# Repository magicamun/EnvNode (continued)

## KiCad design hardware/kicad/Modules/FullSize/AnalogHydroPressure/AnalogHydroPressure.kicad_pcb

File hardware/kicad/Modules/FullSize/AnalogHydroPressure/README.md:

# EnvNode AnalogHydroPressure

`AnalogHydroPressure` is a FullSize daughterboard for a two-wire 4–20 mA hydrostatic pressure probe. The current hardware is Revision 0.5, succeeding the legacy `AnalogInput` module.

## Project Files

- `AnalogHydroPressure.kicad_pro`
- `AnalogHydroPressure.kicad_sch`
- `AnalogHydroPressure.kicad_pcb`
- `Analog.kicad_sch` — analog input and ADS1115
- `24VBoost.kicad_sch` — local probe-supply generation
- `Documentation/AnalogHydroPressure_Bestueckungs_und_Bringup_Rev0.5.pdf` — assembly, configuration, and bring-up guide

## Functional Structure

The module has two hierarchical circuit sections:

- The analog section converts the probe loop current across a 150 ohm, 0.1% burden resistor, filters and clamps the signal, and digitizes it with an `ADS1115IDGS` on the I2C bus selected by JP5 (SDA) and JP6 (SCL).
- The boost section uses an `LT8330S6` to generate the local 24 V probe rail from the module interface's `+5V` supply.

The ADS1115 address is selected with one of four solder jumpers for addresses `0x48` through `0x4B`. Exactly one address jumper must be closed before operation.

JP5 (SDA) and JP6 (SCL) select the ADS1115 bus. Bridge pins 1-2 on both for I2C0, or pins 2-3 on both for I2C1. Both jumpers must select the same bus. Without both bridges the ADS1115 is disconnected from the bus. Never bridge all three pins or mix the bus selections. These jumpers do not select the 5 V supply. The identity EEPROM remains on I2C0.

## Local Libraries

The LT8330 symbol is stored in:

`hardware/kicad/Libraries/EnvNode-Symbols.kicad_sym`

The C&K switch footprint is stored in:

`hardware/kicad/Libraries/EnvNode-Footprints.pretty/SW_Slide_CK_OS202011MS2QS1.kicad_mod`

The project-level `sym-lib-table` maps the symbol library. The footprint library name must resolve as `EnvNode-Footprints` in KiCad.

The analog measurement path remains electrically functional without the identity EEPROM. Without a valid module descriptor, firmware cannot identify the module, validate compatibility or derive module-specific settings. ADC acquisition and boost control then require explicit manual configuration and suitable driver support.

## Bring-up Priorities

1. Populate and inspect the 5 V input and LT8330 boost section.
2. Power it from a current-limited 5 V supply before connecting a probe.
3. Verify startup, switching waveform, output voltage, ripple, and component temperature under the intended load.
4. Verify that exactly one ADS1115 address jumper is closed and that the ADC is detected on the I2C bus selected by JP5 (SDA) and JP6 (SCL).
5. Apply known loop currents and verify approximately 0.6 V at 4 mA and 3.0 V at 20 mA across the nominal 150 ohm burden.
6. Verify the bottom-side U3 (24LC32A-I/SN, ENP-00102) and C1 (100 nF, ENP-00006), the 3.3 V supply and I2C0 address 0x52 (Slot A) or 0x53 (Slot B). Validate the module descriptor; an I2C response alone does not confirm provisioning. Use a matching descriptor, never the DuoRelay template.
7. Calibrate the complete measurement path with the intended pressure probe.

## Validation and Release Status

Revision 0.4 uses the B260S1F-7 boost diode, selectable ADS1115 address jumpers, and an optional DNP measurement header for GND, `+24V`, `LOOP_RETURN`, and `AIN0`. The bottom-side identification EEPROM U3 and its 100 nF decoupling capacitor C1 are part of the standard assembly. J2 remains optional / DNP. The PCB remains Revision 0.5.

At the historical design checkpoint on 2026-09-28, schematic ERC and PCB DRC completed without errors or violations, schematic/PCB parity was clean, and the layout received a visual plausibility review. These checks do not replace physical power-supply bring-up, thermal and EMC verification, probe calibration, or production testing.

The Revision 0.5 assembly/bring-up guide documents AUX_GPIO2 / connector pin 10 for boost enable, including continuity checks, startup sequencing, updated PCB views, and source hashes. Revision 0.4 remains available as a historical guide; its article list predates the enable reassignment. Physical boost-converter validation, thermal and EMC verification, probe calibration, and production testing remain required before production release.

## Connector review — 2026-09-28

The module uses J1 pin 5 for I2C0 SDA and pin 6 for I2C0 SCL. Mini Revision 0.7 and WeatherStation Revision 0.2 both match this assignment in schematic and PCB; the earlier mainboard I2C0 mismatch is resolved for these revisions. I2C1 uses pin 7 SDA and pin 8 SCL and can be selected for the ADS1115 through JP5/JP6.

Revision 0.5 moves LT8330 EN/UVLO and its R7 pull-down to J1 pin 10 / AUX_GPIO2 in both schematic and PCB. J1 pin 9 / AUX_GPIO1 is now unused and available for a future conditioned SCT013 analog signal; no SCT013 circuit is implemented yet. Firmware must use AUX_GPIO2 for boost enable: GPIO13 on Mini Slot A and WeatherStation Slot A, GPIO14 on Mini Slot B. Firmware was not modified as part of this hardware revision.

The Revision 0.5 review on 2026-09-28, with zone refill, found no PCB DRC violations, unconnected pads, or schematic/PCB parity issues. Schematic ERC reports zero errors and ten warnings (unused labelled signals and duplicate local/global label names). The separate connector comparison confirms the corrected I2C0 assignment on Mini Revision 0.7 and WeatherStation Revision 0.2.

## Documentation verification — 2026-10-05

The Revision 0.5 guide was checked against an exported schematic netlist and PCB pad nets. J1.10, U4.4 (EN/UVLO), and R7.1 share AUX_GPIO2; J1.9 remains separate. The PCB views use the common ORing camera angles with preserved proportions. No new full ERC/DRC run or physical validation was performed during this documentation update.

## Documentation update — 2026-10-17

The bottom view and source checksums in the current guide were updated from the saved KiCad project. U3 and C1 are shown populated. No new ERC/DRC run or physical validation was performed for this documentation update.

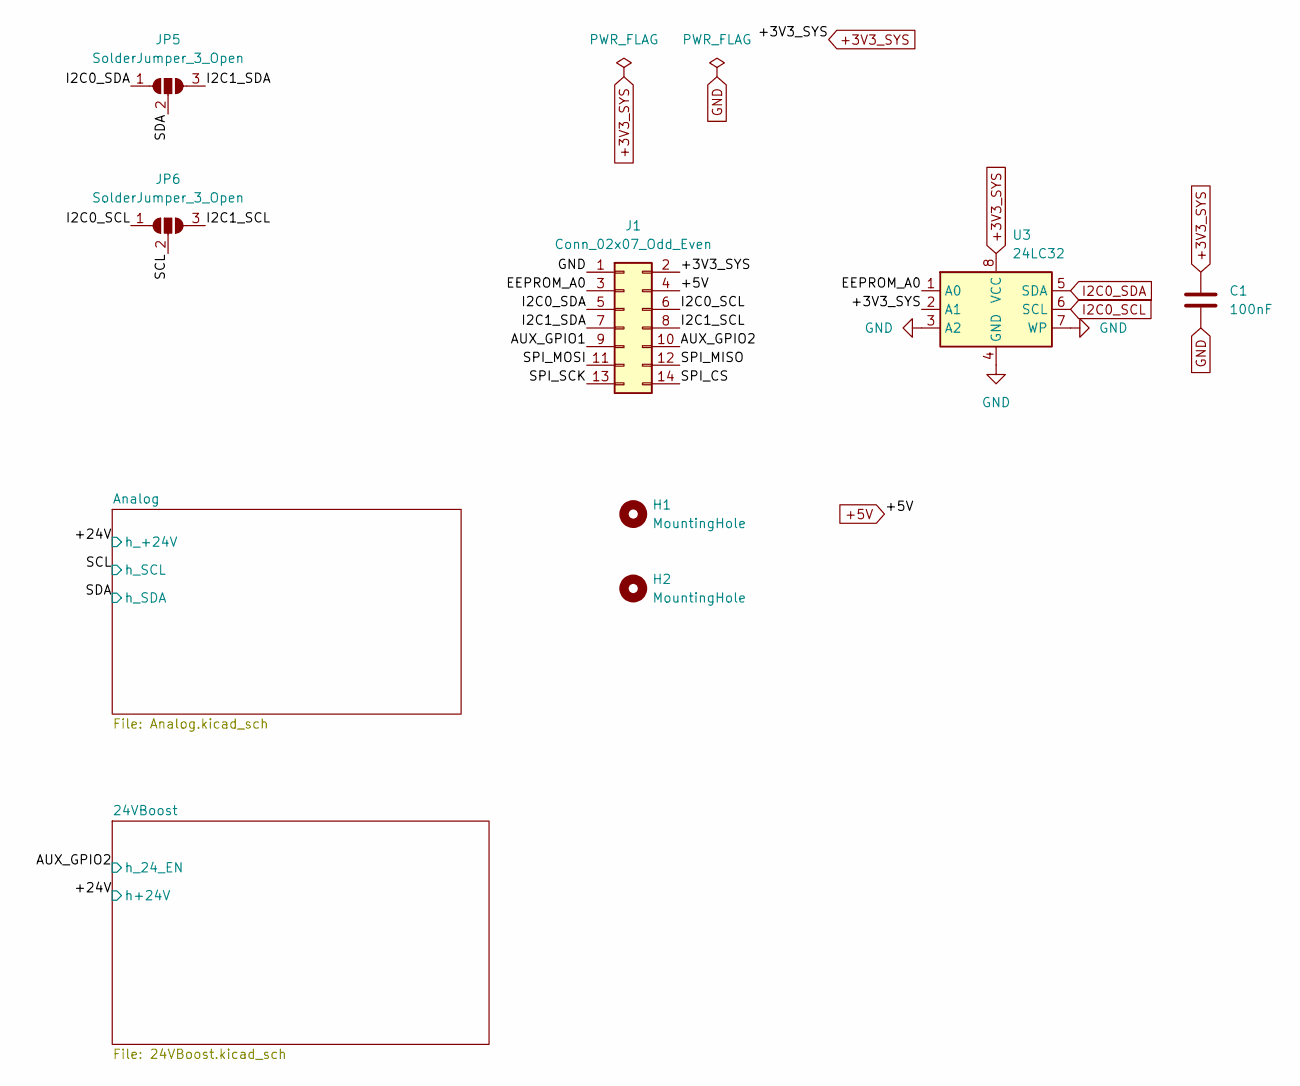
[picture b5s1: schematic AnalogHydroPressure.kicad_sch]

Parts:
C1: 100nF; C_1206_3216Metric_Pad1.33x1.80mm_HandSolder
H1, H2: MountingHole; MountingHole_2.7mm_M2.5_DIN965
J1: Conn_02x07_Odd_Even; PinHeader_2x07_P2.54mm_Vertical_Bottom
JP5, JP6: SolderJumper_3_Open; SolderJumper-3_P1.3mm_Open_RoundedPad1.0x1.5mm_NumberLabels
U3: 24LC32; SOIC-8_3.9x4.9mm_P1.27mm

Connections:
+3V3_SYS: C1.1, J1.2, U3.2 (A1), U3.8 (VCC); also elsewhere on the board
+5V: J1.4; also elsewhere on the board
/AUX_GPIO1: J1.9
/AUX_GPIO2: J1.10; also elsewhere on the board
/EEPROM_A0: J1.3, U3.1 (A0)
/I2C1_SCL: J1.8, JP6.3 (B)
/I2C1_SDA: J1.7, JP5.3 (B)
/SCL: JP6.2 (C); also elsewhere on the board
/SDA: JP5.2 (C); also elsewhere on the board
/SPI_CS: J1.14
/SPI_MISO: J1.12
/SPI_MOSI: J1.11
/SPI_SCK: J1.13
GND: C1.2, J1.1, U3.3 (A2), U3.4 (GND), U3.7 (WP); also elsewhere on the board
I2C0_SCL: J1.6, JP6.1 (A), U3.6 (SCL)
I2C0_SDA: J1.5, JP5.1 (A), U3.5 (SDA)

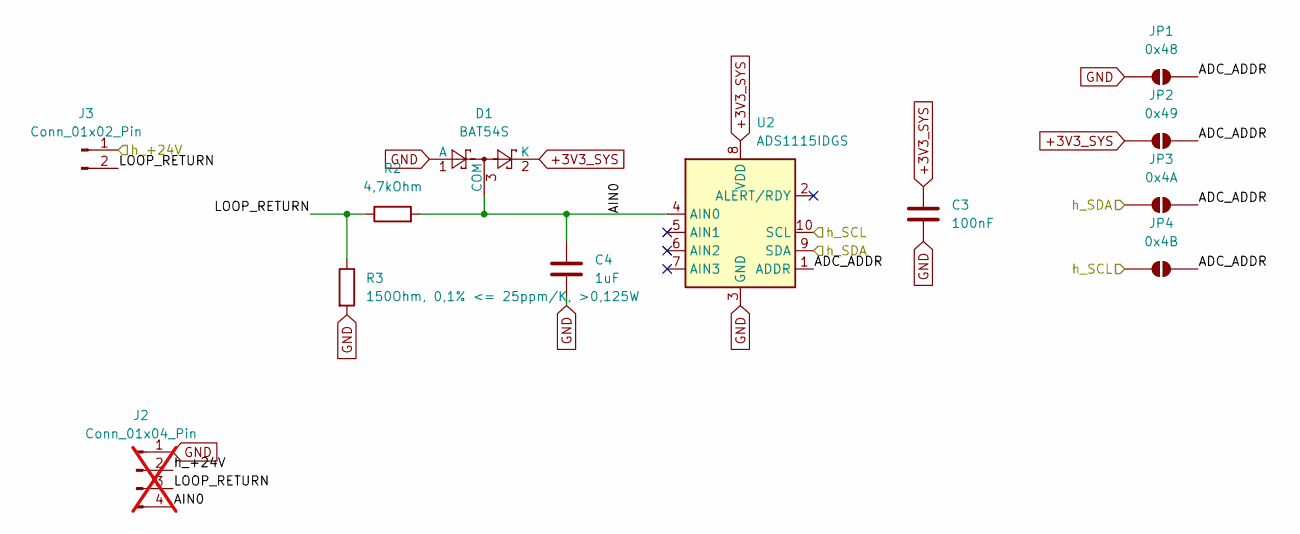
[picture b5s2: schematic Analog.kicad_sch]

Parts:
C3: 100nF; C_1206_3216Metric_Pad1.33x1.80mm_HandSolder
C4: 1uF; C_1206_3216Metric_Pad1.33x1.80mm_HandSolder
D1: BAT54S; SOT-23
J2: Conn_01x04_Pin; PinHeader_1x04_P2.54mm_Vertical; not fitted
J3: Conn_01x02_Pin; JST_PH_B2B-PH-K_1x02_P2.00mm_Vertical
JP1: 0x48; SolderJumper-2_P1.3mm_Open_Pad1.0x1.5mm
JP2: 0x49; SolderJumper-2_P1.3mm_Open_Pad1.0x1.5mm
JP3: 0x4A; SolderJumper-2_P1.3mm_Open_Pad1.0x1.5mm
JP4: 0x4B; SolderJumper-2_P1.3mm_Open_Pad1.0x1.5mm
R2: 4,7kOhm; R_1206_3216Metric_Pad1.30x1.75mm_HandSolder
R3: 150Ohm, 0,1% <= 25ppm/K, >0,125W; R_Axial_DIN0207_L6.3mm_D2.5mm_P7.62mm_Horizontal
U2: ADS1115IDGS; TSSOP-10_3x3mm_P0.5mm

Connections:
+3V3_SYS: C3.1, D1.2 (K), JP2.1 (A), U2.8 (VDD); also elsewhere on the board
/+24V: J2.2, J3.1; also elsewhere on the board
/Analog/ADC_ADDR: JP1.2 (B), JP2.2 (B), JP3.2 (B), JP4.2 (B), U2.1 (ADDR)
/Analog/AIN0: C4.1, D1.3 (COM), J2.4, R2.2, U2.4 (AIN0)
/Analog/LOOP_RETURN: J2.3, J3.2, R2.1, R3.1
/SCL: JP4.1 (A), U2.10 (SCL); also elsewhere on the board
/SDA: JP3.1 (A), U2.9 (SDA); also elsewhere on the board
GND: C3.2, C4.2, D1.1 (A), J2.1, JP1.1 (A), R3.2, U2.3 (GND); also elsewhere on the board

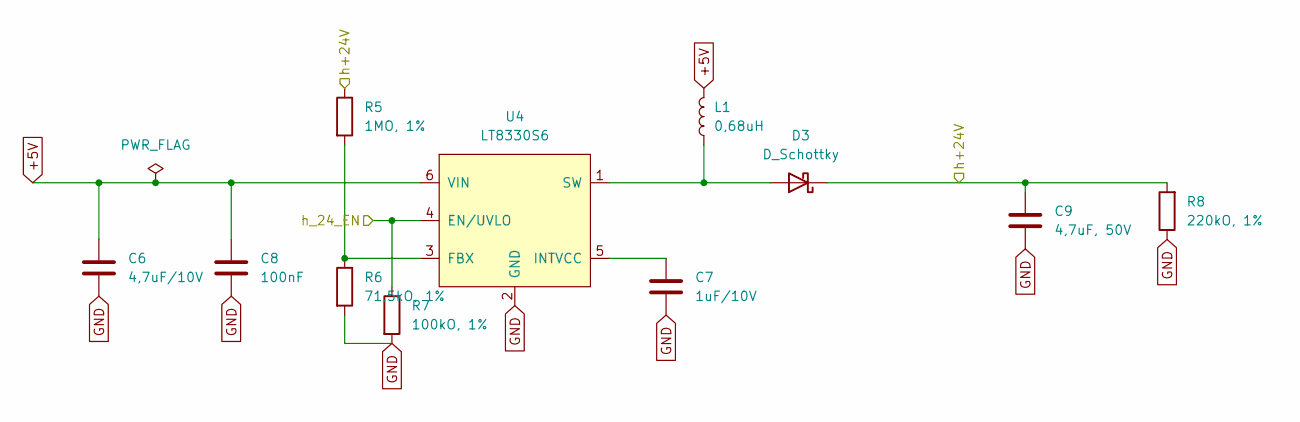
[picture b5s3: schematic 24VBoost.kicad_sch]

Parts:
C6: 4,7uF/10V; C_1206_3216Metric_Pad1.33x1.80mm_HandSolder
C7: 1uF/10V; C_1206_3216Metric_Pad1.33x1.80mm_HandSolder
C8: 100nF; C_1206_3216Metric_Pad1.33x1.80mm_HandSolder
C9: 4,7uF, 50V; C_1210_3225Metric_Pad1.33x2.70mm_HandSolder
D3: D_Schottky; D_SOD-123F
L1: 0,68uH; L_Wuerth_MAPI-3012
R5: 1MO, 1%; R_1206_3216Metric_Pad1.30x1.75mm_HandSolder
R6: 71,5kO, 1%; R_1206_3216Metric_Pad1.30x1.75mm_HandSolder
R7: 100kO, 1%; R_1206_3216Metric_Pad1.30x1.75mm_HandSolder
R8: 220kO, 1%; R_1206_3216Metric_Pad1.30x1.75mm_HandSolder
U4: LT8330S6; SOT-23-6

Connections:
+5V: C6.1, C8.1, L1.2, U4.6 (VIN); also elsewhere on the board
/+24V: C9.1, D3.1 (K), R5.1, R8.2; also elsewhere on the board
/AUX_GPIO2: R7.1, U4.4 (EN/UVLO); also elsewhere on the board
GND: C6.2, C7.2, C8.2, C9.2, R6.2, R7.2, R8.1, U4.2 (GND); also elsewhere on the board
unnamed: D3.2 (A), L1.1, U4.1 (SW)
unnamed: R5.2, R6.1, U4.3 (FBX)
unnamed: C7.1, U4.5 (INTVCC)

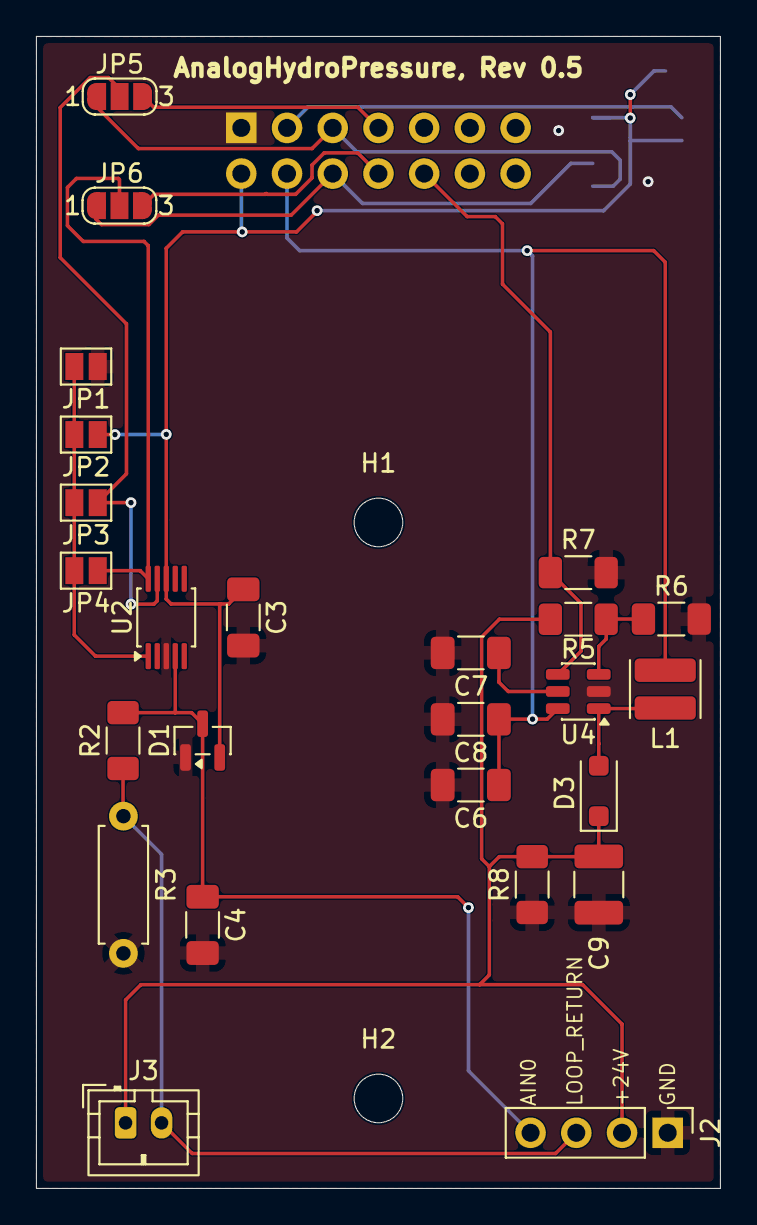
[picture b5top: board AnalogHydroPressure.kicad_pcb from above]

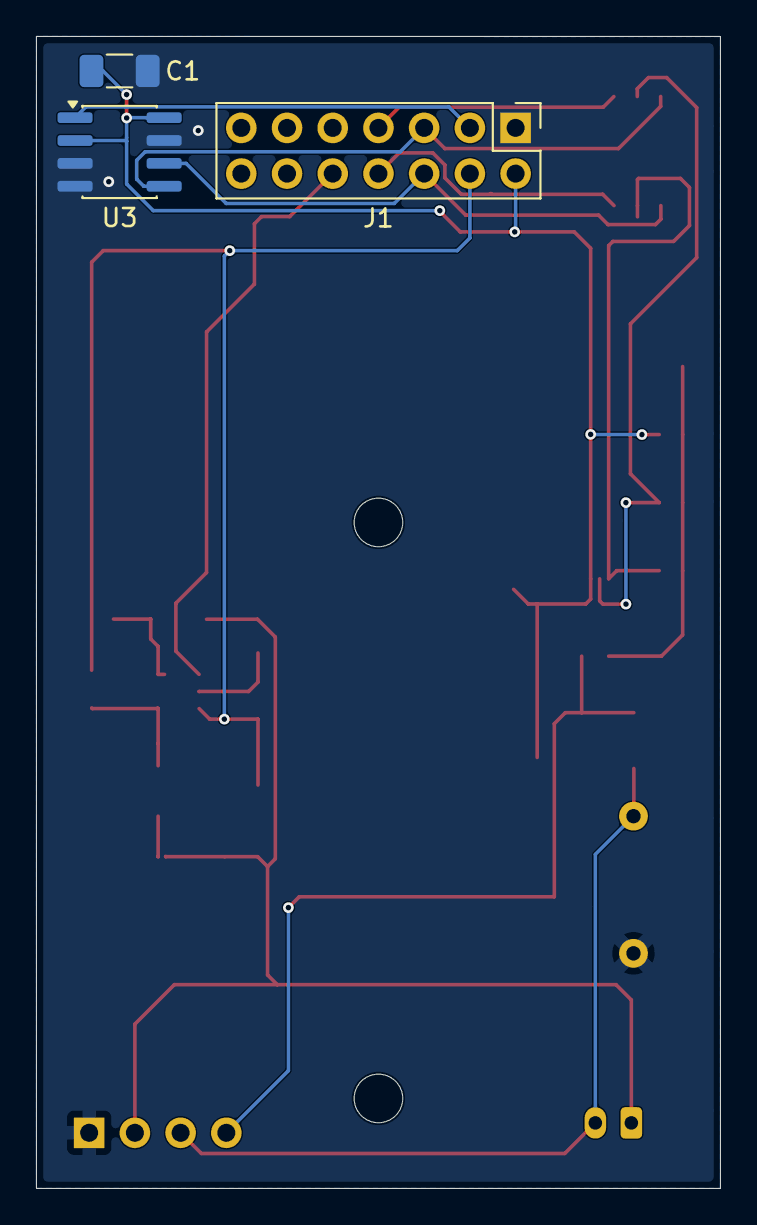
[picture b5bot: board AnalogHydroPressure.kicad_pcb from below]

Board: 2 copper layers, 38.0 x 64.0 mm, 30 parts (3 on the bottom side), 18 nets.

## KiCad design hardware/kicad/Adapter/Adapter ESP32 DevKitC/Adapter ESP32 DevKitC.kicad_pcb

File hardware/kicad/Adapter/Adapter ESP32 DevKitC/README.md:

# ESP32 DevKitC Adapter — revision 0.3

EnvNode-owned material: see the repository LICENSE.

40 measurement inputs: J2 has 38 socket pins (2×19, pitch 2.54 mm, row spacing
25.40 mm), TP1/2 is MB_3V3_SYS and TP1/1 is MB_GND. J1 connects pin-for-pin to
[Test Controller](../../MainBoards/Test-Controller/README.md) J8.

Select **ESP32 DevKitC Adapter 0.3** in tester firmware before measuring. Its mapping
differs from the [Legacy Input Adapter](../Input-Adapter/README.md). Both controller
revisions are supported. The generated mapping and PCB SHA-256 are recorded in
`firmware/testboard/fixture-esp32-devkitc0.3.json` at the repository root.

Supply 3V3_SYS/GND through J1. Keep all DUT/reference contacts isolated from supply
GND. Remove the target ESP32 and all target power before passive testing.

## Revision status

CAD and electrical routing reviewed; physical commissioning remains pending.
The title text may still mention S3; the saved J2 footprint is the 38-contact
ESP32 DevKitC variant. No 44-contact S3 adapter profile is enabled in the firmware.

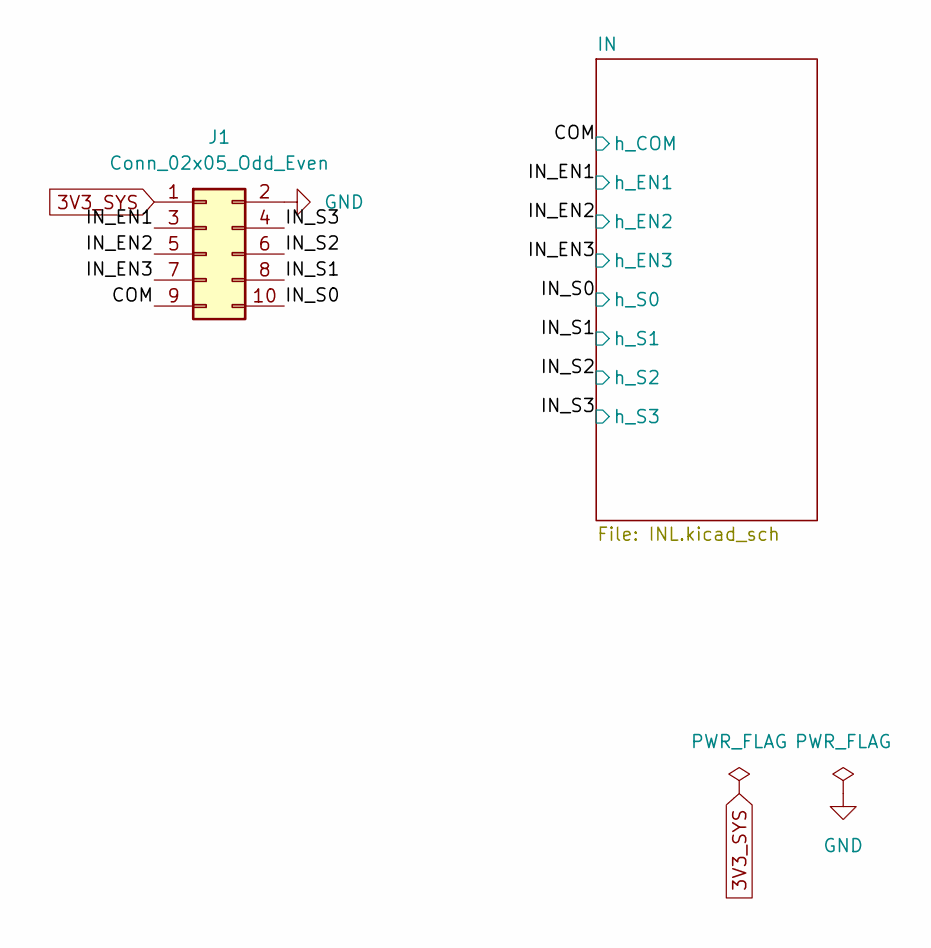
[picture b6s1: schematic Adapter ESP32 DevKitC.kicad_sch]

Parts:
J1: Conn_02x05_Odd_Even; IDC-Header_2x05_P2.54mm_Vertical

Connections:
3V3_SYS: J1.1; also elsewhere on the board
/COM: J1.9; also elsewhere on the board
/IN_EN1: J1.3; also elsewhere on the board
/IN_EN2: J1.5; also elsewhere on the board
/IN_EN3: J1.7; also elsewhere on the board
/IN_S0: J1.10; also elsewhere on the board
/IN_S1: J1.8; also elsewhere on the board
/IN_S2: J1.6; also elsewhere on the board
/IN_S3: J1.4; also elsewhere on the board
GND: J1.2; also elsewhere on the board

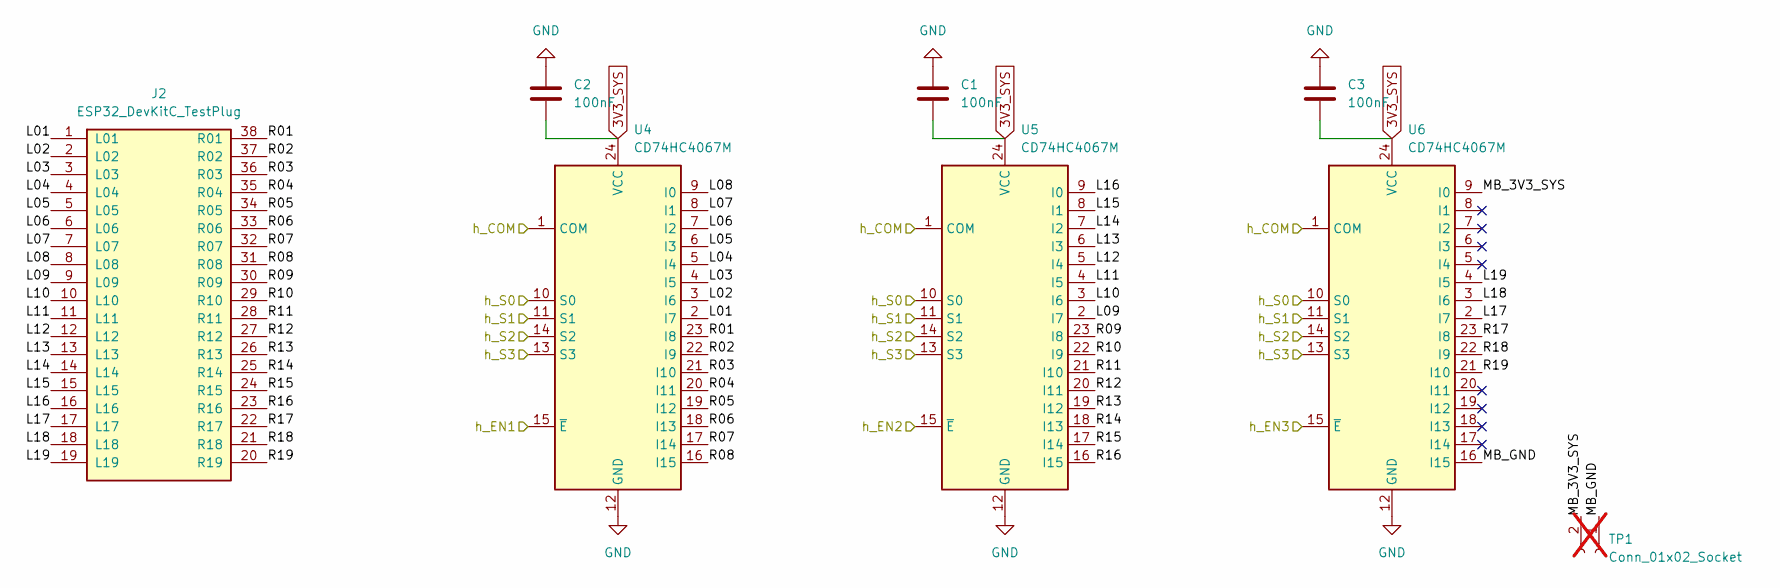
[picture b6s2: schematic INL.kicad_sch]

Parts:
C1, C2, C3: 100nF; C_1206_3216Metric_Pad1.33x1.80mm_HandSolder
J2: ESP32_DevKitC_TestPlug; ESP32_DevKitC_TestPlug_2x19_P2.54mm_Row25.40mm
TP1: Conn_01x02_Socket; PinHeader_1x02_P2.54mm_Vertical; not fitted
U4, U5, U6: CD74HC4067M; SOIC-24W_7.5x15.4mm_P1.27mm

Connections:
3V3_SYS: C1.2, C2.2, C3.2, U4.24 (VCC), U5.24 (VCC), U6.24 (VCC); also elsewhere on the board
/COM: U4.1 (COM), U5.1 (COM), U6.1 (COM); also elsewhere on the board
/IN/L01: J2.1 (L01), U4.2 (I7)
/IN/L02: J2.2 (L02), U4.3 (I6)
/IN/L03: J2.3 (L03), U4.4 (I5)
/IN/L04: J2.4 (L04), U4.5 (I4)
/IN/L05: J2.5 (L05), U4.6 (I3)
/IN/L06: J2.6 (L06), U4.7 (I2)
/IN/L07: J2.7 (L07), U4.8 (I1)
/IN/L08: J2.8 (L08), U4.9 (I0)
/IN/L09: J2.9 (L09), U5.2 (I7)
/IN/L10: J2.10 (L10), U5.3 (I6)
/IN/L11: J2.11 (L11), U5.4 (I5)
/IN/L12: J2.12 (L12), U5.5 (I4)
/IN/L13: J2.13 (L13), U5.6 (I3)
/IN/L14: J2.14 (L14), U5.7 (I2)
/IN/L15: J2.15 (L15), U5.8 (I1)
/IN/L16: J2.16 (L16), U5.9 (I0)
/IN/L17: J2.17 (L17), U6.2 (I7)
/IN/L18: J2.18 (L18), U6.3 (I6)
/IN/L19: J2.19 (L19), U6.4 (I5)
/IN/MB_3V3_SYS: TP1.2, U6.9 (I0)
/IN/MB_GND: TP1.1, U6.16 (I15)
/IN/R01: J2.38 (R01), U4.23 (I8)
/IN/R02: J2.37 (R02), U4.22 (I9)
/IN/R03: J2.36 (R03), U4.21 (I10)
/IN/R04: J2.35 (R04), U4.20 (I11)
/IN/R05: J2.34 (R05), U4.19 (I12)
/IN/R06: J2.33 (R06), U4.18 (I13)
/IN/R07: J2.32 (R07), U4.17 (I14)
/IN/R08: J2.31 (R08), U4.16 (I15)
/IN/R09: J2.30 (R09), U5.23 (I8)
/IN/R10: J2.29 (R10), U5.22 (I9)
/IN/R11: J2.28 (R11), U5.21 (I10)
/IN/R12: J2.27 (R12), U5.20 (I11)
/IN/R13: J2.26 (R13), U5.19 (I12)
/IN/R14: J2.25 (R14), U5.18 (I13)
/IN/R15: J2.24 (R15), U5.17 (I14)
/IN/R16: J2.23 (R16), U5.16 (I15)
/IN/R17: J2.22 (R17), U6.23 (I8)
/IN/R18: J2.21 (R18), U6.22 (I9)
/IN/R19: J2.20 (R19), U6.21 (I10)
/IN_EN1: U4.15 (~E); also elsewhere on the board
/IN_EN2: U5.15 (~E); also elsewhere on the board
/IN_EN3: U6.15 (~E); also elsewhere on the board
/IN_S0: U4.10 (S0), U5.10 (S0), U6.10 (S0); also elsewhere on the board
/IN_S1: U4.11 (S1), U5.11 (S1), U6.11 (S1); also elsewhere on the board
/IN_S2: U4.14 (S2), U5.14 (S2), U6.14 (S2); also elsewhere on the board
/IN_S3: U4.13 (S3), U5.13 (S3), U6.13 (S3); also elsewhere on the board
GND: C1.1, C2.1, C3.1, U4.12 (GND), U5.12 (GND), U6.12 (GND); also elsewhere on the board

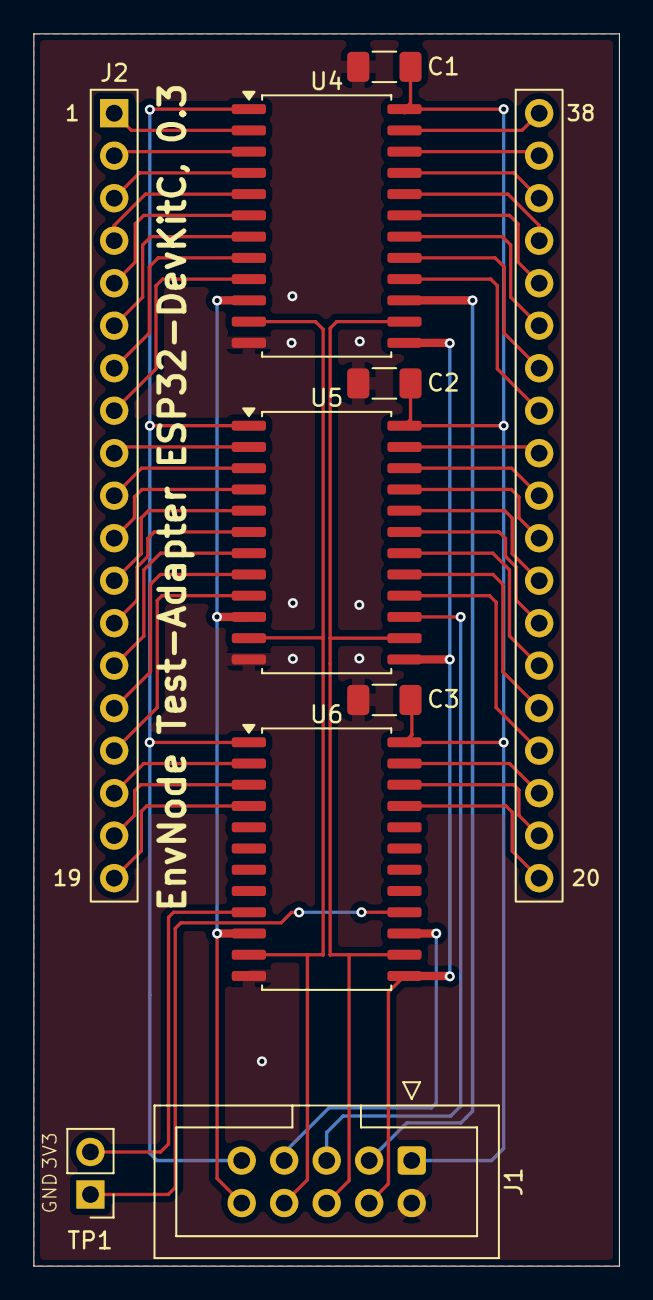
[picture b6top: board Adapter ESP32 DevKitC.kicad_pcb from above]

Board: 2 copper layers, 35.0 x 73.7 mm, 9 parts (0 on the bottom side), 50 nets.

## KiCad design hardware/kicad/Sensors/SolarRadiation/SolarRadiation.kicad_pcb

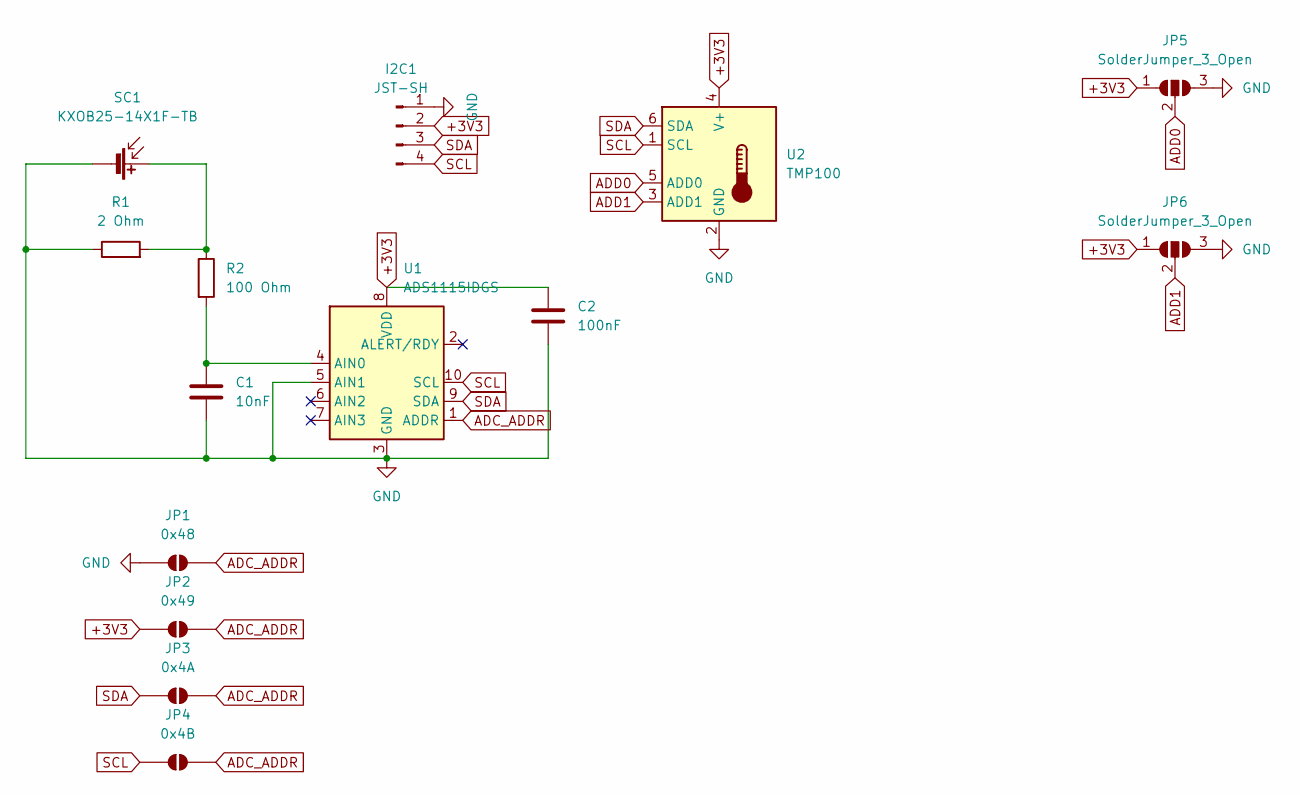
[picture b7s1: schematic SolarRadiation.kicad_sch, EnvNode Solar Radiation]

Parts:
C1: 10nF; C_1206_3216Metric_Pad1.33x1.80mm_HandSolder
C2: 100nF; C_1206_3216Metric_Pad1.33x1.80mm_HandSolder
I2C1: JST-SH; JST_SH_SM04B-SRSS-TB_1x04-1MP_P1.00mm_Horizontal
JP1: 0x48; SolderJumper-2_P1.3mm_Open_Pad1.0x1.5mm
JP2: 0x49; SolderJumper-2_P1.3mm_Open_Pad1.0x1.5mm
JP3: 0x4A; SolderJumper-2_P1.3mm_Open_Pad1.0x1.5mm
JP4: 0x4B; SolderJumper-2_P1.3mm_Open_Pad1.0x1.5mm
JP5, JP6: SolderJumper_3_Open; SolderJumper-3_P1.3mm_Open_RoundedPad1.0x1.5mm_NumberLabels
R1: 2 Ohm; R_Axial_DIN0207_L6.3mm_D2.5mm_P7.62mm_Horizontal
R2: 100 Ohm; R_1206_3216Metric_Pad1.30x1.75mm_HandSolder
SC1: KXOB25-14X1F-TB; KXOB25-14X1F
U1: ADS1115IDGS; TSSOP-10_3x3mm_P0.5mm
U2: TMP100; SOT-23-6

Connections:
+3V3: C2.1, I2C1.2, JP2.1 (A), JP5.1 (A), JP6.1 (A), U1.8 (VDD), U2.4 (V+)
ADC_ADDR: JP1.2 (B), JP2.2 (B), JP3.2 (B), JP4.2 (B), U1.1 (ADDR)
ADD0: JP5.2 (C), U2.5 (ADD0)
ADD1: JP6.2 (C), U2.3 (ADD1)
GND: C1.2, C2.2, I2C1.1, JP1.1 (A), JP5.3 (B), JP6.3 (B), R1.1, SC1.2 (-), U1.3 (GND), U1.5 (AIN1), U2.2 (GND)
unnamed: R1.2, R2.1, SC1.1 (+)
unnamed: C1.1, R2.2, U1.4 (AIN0)
SCL: I2C1.4, JP4.1 (A), U1.10 (SCL), U2.1 (SCL)
SDA: I2C1.3, JP3.1 (A), U1.9 (SDA), U2.6 (SDA)

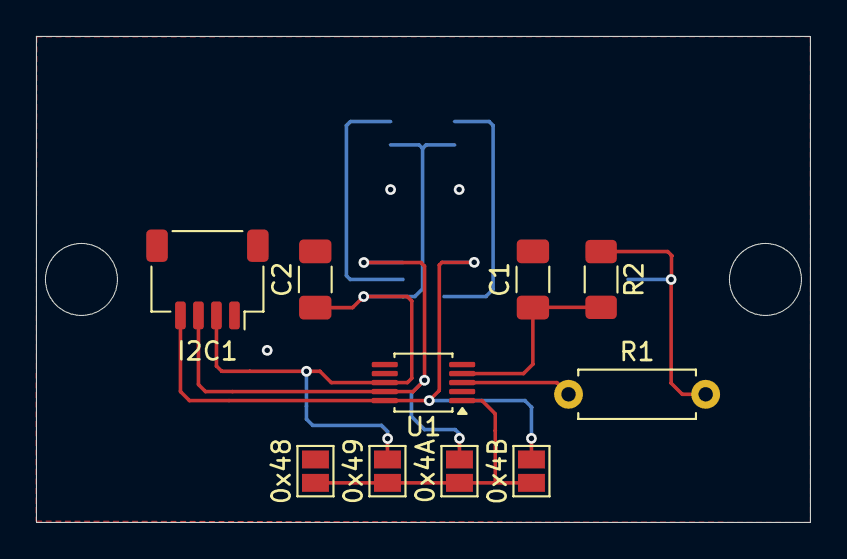
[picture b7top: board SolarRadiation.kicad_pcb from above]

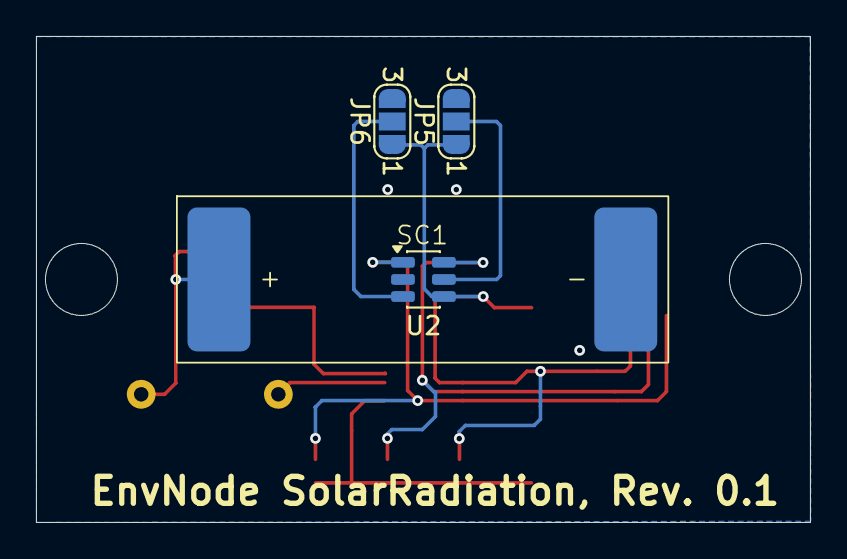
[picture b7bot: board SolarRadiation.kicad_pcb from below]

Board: 2 copper layers, 43.0 x 27.0 mm, 14 parts (4 on the bottom side), 9 nets.

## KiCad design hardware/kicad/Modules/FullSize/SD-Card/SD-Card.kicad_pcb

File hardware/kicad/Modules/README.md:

# EnvNode Revision 0.3 Modules

This directory contains the current module templates and functional daughterboards for the EnvNode Revision 0.3 module interface. The electrical connector contract was introduced with Revision 0.2 and is retained by the current Revision 0.3 designs.

## Functional Modules

- [FullSize/AnalogHydroPressure](FullSize/AnalogHydroPressure/README.md): ADS1115-based 4–20 mA pressure input with a local 5 V to 24 V boost supply.
- [FullSize/DuoRelay](FullSize/DuoRelay/README.md): two independently controlled 5 V changeover relays.

## Starting Templates

| Size | Bottom-mounted connector |
| --- | --- |
| [FullSize/Empty-SMD](FullSize/Empty-SMD/README.md) | SMD |
| [FullSize/Empty-THT](FullSize/Empty-THT/README.md) | THT |
| [HalfSize/Empty-SMD](HalfSize/Empty-SMD/README.md) | SMD |
| [HalfSize/Empty-THT](HalfSize/Empty-THT/README.md) | THT |

New modules must follow the [module-interface hardware specification](../../../docs/EnvNode_Module_Interface_Hardware_Specification.md). Copy the appropriate template instead of modifying it in place, preserve the connector pin mapping and mechanical reference geometry, and rerun ERC and DRC after every functional or layout change.

## Release Status

Revision 0.3 is not yet released for production. Release requires a complete article list and assembly information, physical bring-up of the relevant boards, and successful operation of at least the Rain Detector heater path. A later provisioning station is intended to prepare Mainboards, Modules, and other supported boards with their identities and required initial data.

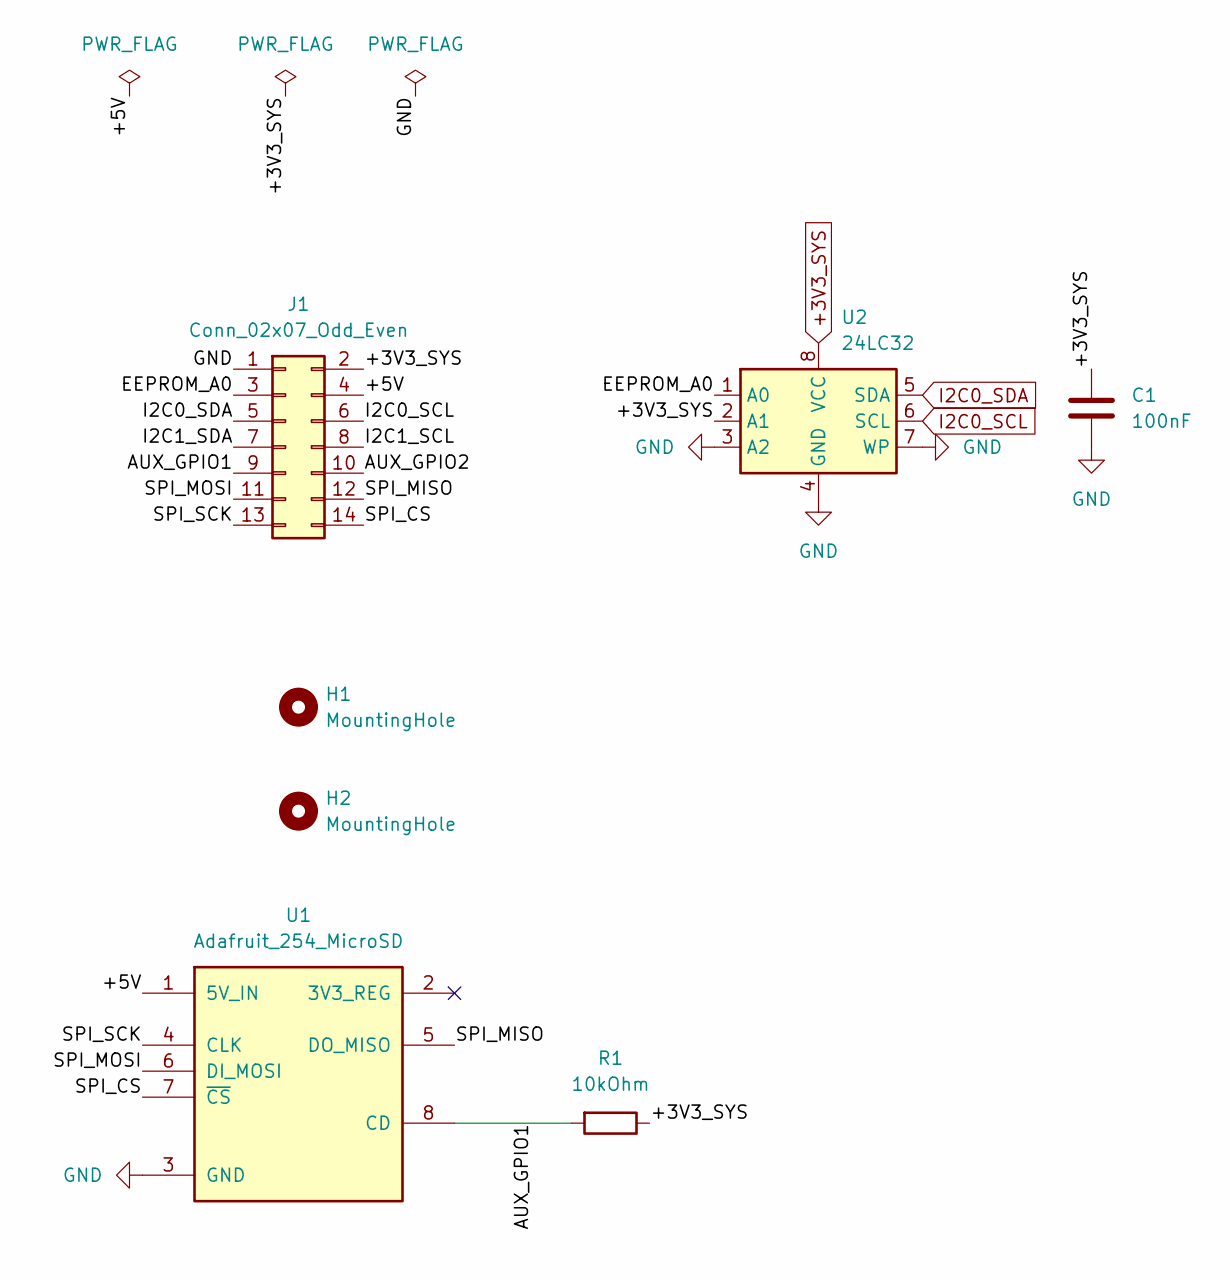
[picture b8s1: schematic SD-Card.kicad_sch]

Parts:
C1: 100nF; C_1206_3216Metric_Pad1.33x1.80mm_HandSolder
H1, H2: MountingHole; MountingHole_2.7mm_M2.5_DIN965
J1: Conn_02x07_Odd_Even; PinHeader_2x07_P2.54mm_Vertical_Bottom
R1: 10kOhm; R_1206_3216Metric_Pad1.30x1.75mm_HandSolder
U1: Adafruit_254_MicroSD
U2: 24LC32; SOIC-8_3.9x4.9mm_P1.27mm

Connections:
+3V3_SYS: C1.1, J1.2, R1.1, U2.2 (A1), U2.8 (VCC)
/+5V: J1.4, U1.1 (5V_IN)
/AUX_GPIO1: J1.9, R1.2, U1.8 (CD)
/AUX_GPIO2: J1.10
/EEPROM_A0: J1.3, U2.1 (A0)
/I2C1_SCL: J1.8
/I2C1_SDA: J1.7
/SPI_CS: J1.14, U1.7 (~CS)
/SPI_MISO: J1.12, U1.5 (DO_MISO)
/SPI_MOSI: J1.11, U1.6 (DI_MOSI)
/SPI_SCK: J1.13, U1.4 (CLK)
GND: C1.2, J1.1, U1.3 (GND), U2.3 (A2), U2.4 (GND), U2.7 (WP)
I2C0_SCL: J1.6, U2.6 (SCL)
I2C0_SDA: J1.5, U2.5 (SDA)

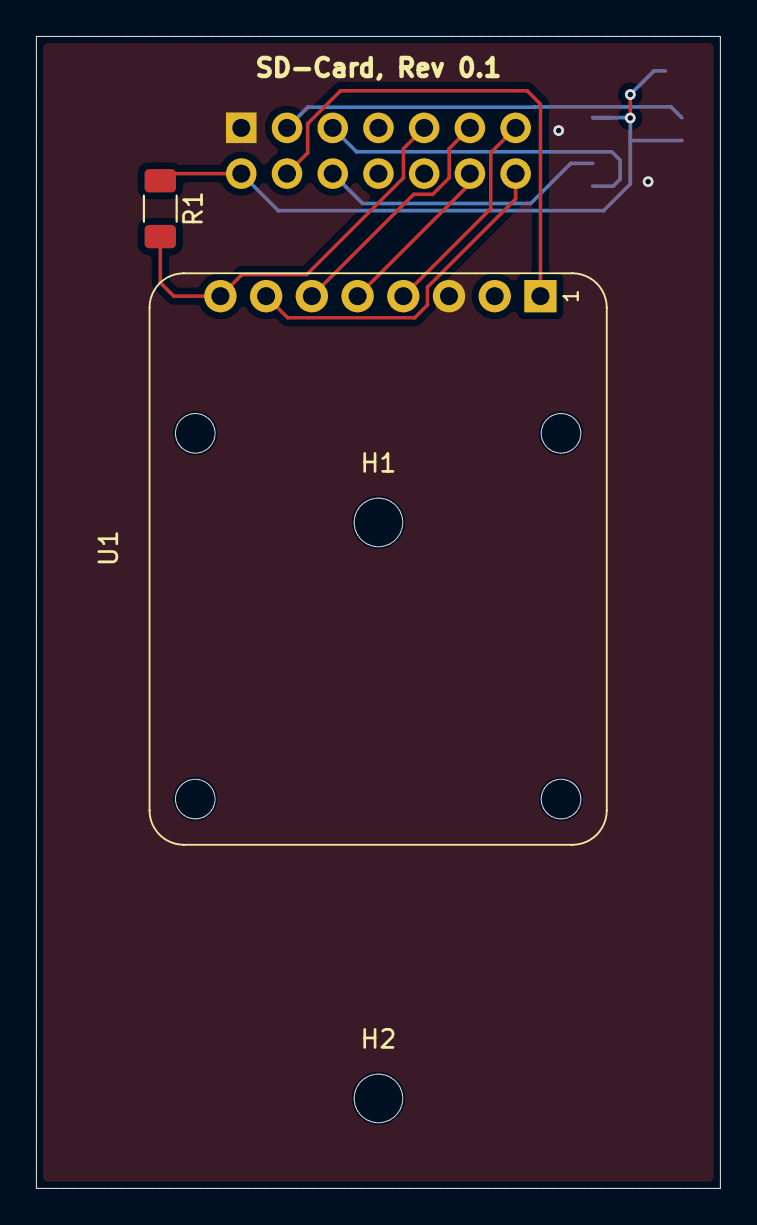
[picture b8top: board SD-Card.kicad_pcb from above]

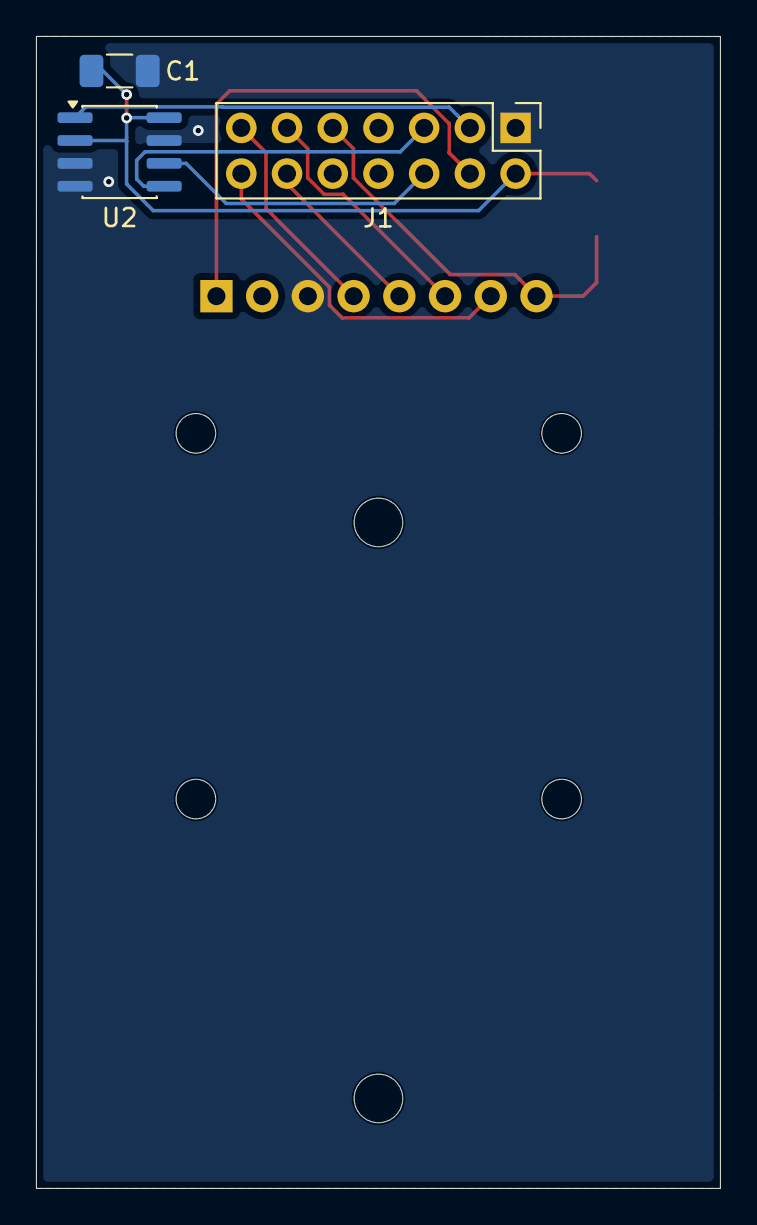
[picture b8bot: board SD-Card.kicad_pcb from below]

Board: 2 copper layers, 38.0 x 64.0 mm, 7 parts (3 on the bottom side), 11 nets.
